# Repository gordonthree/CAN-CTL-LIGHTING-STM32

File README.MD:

# Interior Lighting Controller
Compact lighting controller module intended to interface with three-channel PWM dimmable lighting modules. This module works with other CAN-CTL modules using the robust CAN bus interface.

* STM32G0B1RCT6 Microcontroller, 256k flash, 64mhz clock
* Automotive grade switch-mode power supply for 5v rail
* Automotive grade low-dropout linear supply for 3.3v rail
* 3-pin terminal block for CAN bus connection with drain
* Jumper selected CAN terminator resistor
* Four five position screw terminal connectors for 12v lighting modules
* 12 digital output channels in groups of 3, driven at 5v by hex schmitt line drivers
* Two LED indicators for status, controlled by the micro
* Bidirectional transient voltage protection diode for harsh environments
* Headers for USART1 serial port and SWD programming connector

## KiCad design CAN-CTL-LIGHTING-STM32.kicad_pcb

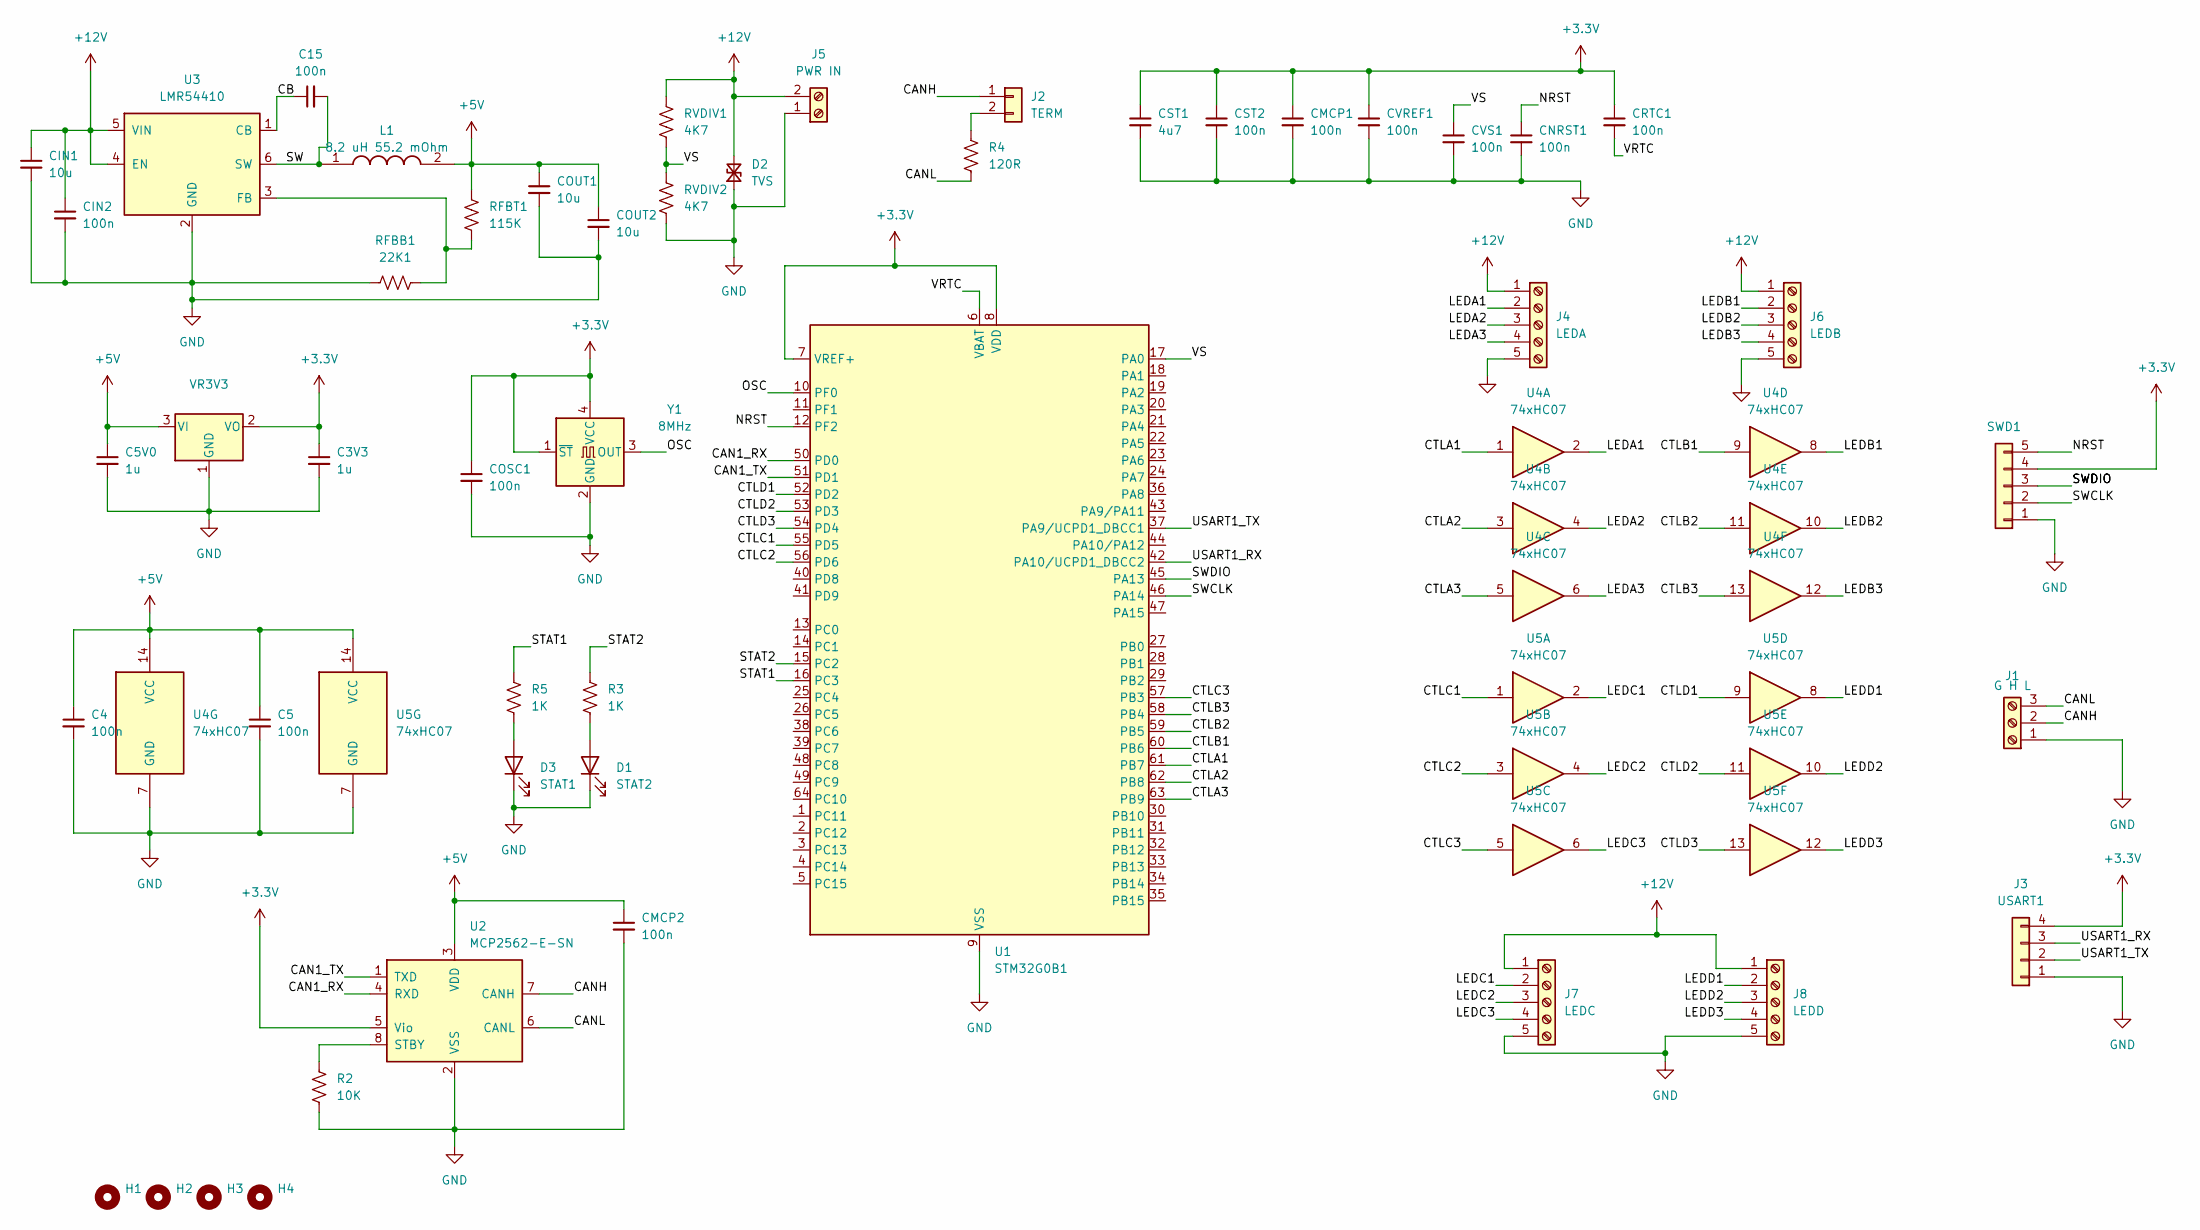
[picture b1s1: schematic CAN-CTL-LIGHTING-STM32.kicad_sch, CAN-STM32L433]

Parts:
C3V3, C5V0: 1u; C_0805_2012Metric_Pad1.18x1.45mm_HandSolder
C4, C5, C15: 100n; C_0603_1608Metric_Pad1.08x0.95mm_HandSolder
CIN1: 10u; C_1210_3225Metric_Pad1.33x2.70mm_HandSolder
CIN2: 100n; C_0603_1608Metric_Pad1.08x0.95mm_HandSolder
CMCP1, CMCP2: 100n; C_0603_1608Metric_Pad1.08x0.95mm_HandSolder
CNRST1: 100n; C_0603_1608Metric_Pad1.08x0.95mm_HandSolder
COSC1: 100n; C_0603_1608Metric_Pad1.08x0.95mm_HandSolder
COUT1, COUT2: 10u; C_0805_2012Metric_Pad1.18x1.45mm_HandSolder
CRTC1: 100n; C_0603_1608Metric_Pad1.08x0.95mm_HandSolder
CST1: 4u7; C_0805_2012Metric_Pad1.18x1.45mm_HandSolder
CST2: 100n; C_0603_1608Metric_Pad1.08x0.95mm_HandSolder
CVREF1: 100n; C_0603_1608Metric_Pad1.08x0.95mm_HandSolder
CVS1: 100n; C_0603_1608Metric_Pad1.08x0.95mm_HandSolder
D1: STAT2; LED_0805_2012Metric_Pad1.15x1.40mm_HandSolder
D2: TVS; D_SMA_Handsoldering
D3: STAT1; LED_0805_2012Metric_Pad1.15x1.40mm_HandSolder
H1, H2, H3, H4: MountingHole; MountingHole_3.2mm_M3_DIN965
J1: G H L; TerminalBlock_Phoenix_MPT-0,5-3-2.54_1x03_P2.54mm_Horizontal
J2: TERM; PinHeader_1x02_P2.54mm_Vertical
J3: USART1; PinHeader_1x04_P2.54mm_Vertical
J4: LEDA; TerminalBlock_Phoenix_MPT-0,5-5-2.54_1x05_P2.54mm_Horizontal
J5: PWR IN; TerminalBlock_Phoenix_MKDS-1,5-2_1x02_P5.00mm_Horizontal
J6: LEDB; TerminalBlock_Phoenix_MPT-0,5-5-2.54_1x05_P2.54mm_Horizontal
J7: LEDC; TerminalBlock_Phoenix_MPT-0,5-5-2.54_1x05_P2.54mm_Horizontal
J8: LEDD; TerminalBlock_Phoenix_MPT-0,5-5-2.54_1x05_P2.54mm_Horizontal
L1: 8.2 uH 55.2 mOhm; SRP5030HMT2R2M; Mouser Part Number SRP5030HMT-8R2M
R2: 10K; R_0603_1608Metric_Pad0.98x0.95mm_HandSolder
R3, R5: 1K; R_0603_1608Metric_Pad0.98x0.95mm_HandSolder
R4: 120R; R_Axial_DIN0207_L6.3mm_D2.5mm_P7.62mm_Horizontal
RFBB1: 22K1; R_0603_1608Metric_Pad0.98x0.95mm_HandSolder
RFBT1: 115K; R_0603_1608Metric_Pad0.98x0.95mm_HandSolder
RVDIV1, RVDIV2: 4K7; R_0603_1608Metric_Pad0.98x0.95mm_HandSolder
SWD1: SWD; PinHeader_1x05_P2.54mm_Vertical
U1: STM32G0B1; LQFP-64_10x10mm_P0.5mm; Manf Part STM32G0B1RCT6
U2: MCP2562-E-SN; SOIC-8_3.9x4.9mm_P1.27mm
U3: LMR54410; SOT-23-6
U4, U5: 74xHC07; SOIC-14_3.9x8.7mm_P1.27mm
VR3V3: TLV1117-33; SOT-223-3_TabPin2
Y1: 8MHz; Oscillator_SMD_EuroQuartz_XO32-4Pin_3.2x2.5mm_RotB_HandSold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

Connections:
+3.3V: C3V3.1, CMCP1.1, COSC1.1, CRTC1.1, CST1.1, CST2.1, CVREF1.1, J3.4, SWD1.4, U1.7 (VREF+), U1.8 (VDD), U2.5 (Vio), VR3V3.2 (VO), Y1.1 (~ST), Y1.4 (VCC)
+5V: C4.1, C5.1, C5V0.1, CMCP2.1, COUT1.1, COUT2.1, L1.2, RFBT1.1, U2.3 (VDD), U4.14 (VCC), U5.14 (VCC), VR3V3.3 (VI)
+12V: CIN1.1, CIN2.1, D2.2 (A2), J4.1, J5.2, J6.1, J7.1, J8.1, RVDIV1.1, U3.4 (EN), U3.5 (VIN)
/CAN1_RX: U1.50 (PD0), U2.4 (RXD)
/CAN1_TX: U1.51 (PD1), U2.1 (TXD)
/CANH: J1.2, J2.1, U2.7 (CANH)
/CANL: J1.3, R4.2, U2.6 (CANL)
/CB: C15.1, U3.1 (CB)
/CTLA1: U1.61 (PB7), U4.1
/CTLA2: U1.62 (PB8), U4.3
/CTLA3: U1.63 (PB9), U4.5
/CTLB1: U1.60 (PB6), U4.9
/CTLB2: U1.59 (PB5), U4.11
/CTLB3: U1.58 (PB4), U4.13
/CTLC1: U1.55 (PD5), U5.1
/CTLC2: U1.56 (PD6), U5.3
/CTLC3: U1.57 (PB3), U5.5
/CTLD1: U1.52 (PD2), U5.9
/CTLD2: U1.53 (PD3), U5.11
/CTLD3: U1.54 (PD4), U5.13
/LEDA1: J4.2, U4.2
/LEDA2: J4.3, U4.4
/LEDA3: J4.4, U4.6
/LEDB1: J6.2, U4.8
/LEDB2: J6.3, U4.10
/LEDB3: J6.4, U4.12
/LEDC1: J7.2, U5.2
/LEDC2: J7.3, U5.4
/LEDC3: J7.4, U5.6
/LEDD1: J8.2, U5.8
/LEDD2: J8.3, U5.10
/LEDD3: J8.4, U5.12
/NRST: CNRST1.1, SWD1.5, U1.12 (PF2)
/OSC: U1.10 (PF0), Y1.3 (OUT)
/STAT1: R5.2, U1.16 (PC3)
/STAT2: R3.2, U1.15 (PC2)
/SW: C15.2, L1.1, U3.6 (SW)
/SWCLK: SWD1.2, U1.46 (PA14)
/SWDIO: SWD1.3, U1.45 (PA13)
/USART1_RX: J3.3, U1.42 (PA10/UCPD1_DBCC2)
/USART1_TX: J3.2, U1.37 (PA9/UCPD1_DBCC1)
/VRTC: CRTC1.2, U1.6 (VBAT)
/VS: CVS1.1, RVDIV1.2, RVDIV2.1, U1.17 (PA0)
GND: C3V3.2, C4.2, C5.2, C5V0.2, CIN1.2, CIN2.2, CMCP1.2, CMCP2.2, CNRST1.2, COSC1.2, COUT1.2, COUT2.2, CST1.2, CST2.2, CVREF1.2, CVS1.2, D1.1 (K), D2.1 (A1), D3.1 (K), J1.1, J3.1, J4.5, J5.1, J6.5, J7.5, J8.5, R2.2, RFBB1.1, RVDIV2.2, SWD1.1, U1.9 (VSS), U2.2 (VSS), U3.2 (GND), U4.7 (GND), U5.7 (GND), VR3V3.1 (GND), Y1.2 (GND)
unnamed: D1.2 (A), R3.1
unnamed: D3.2 (A), R5.1
unnamed: J2.2, R4.1
unnamed: R2.1, U2.8 (STBY)
unnamed: RFBB1.2, RFBT1.2, U3.3 (FB)

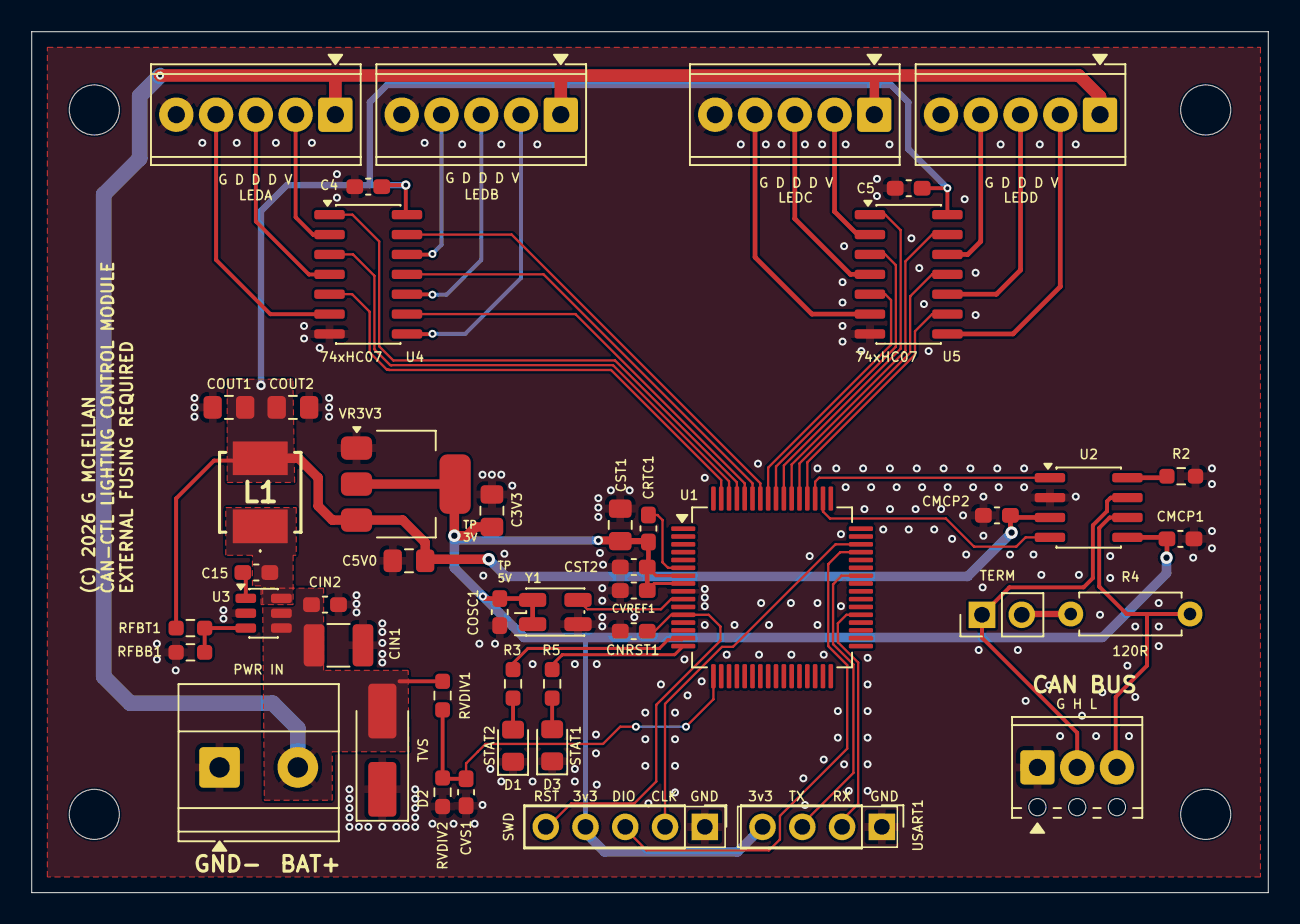
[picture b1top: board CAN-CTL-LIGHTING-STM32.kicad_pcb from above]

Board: 2 copper layers, 79.0 x 55.0 mm, 50 parts (0 on the bottom side), 49 nets.

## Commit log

2026-01-25 update readme details
2026-01-25 update controller details
2026-01-25 drc passed
2026-01-25 silkscreen updates, swapped ground and H on can connector
2026-01-25 updated embedded image url
2026-01-25 wrong url, updated embedded image again
2026-01-25 eliminated second heading
2026-01-31 added copyright text
2026-01-31 tweak the readme
2026-02-02 added crystal osc

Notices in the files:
CAN-CTL-LIGHTING-STM32.kicad_pcb:
(C) 2026 G MCLELLAN
